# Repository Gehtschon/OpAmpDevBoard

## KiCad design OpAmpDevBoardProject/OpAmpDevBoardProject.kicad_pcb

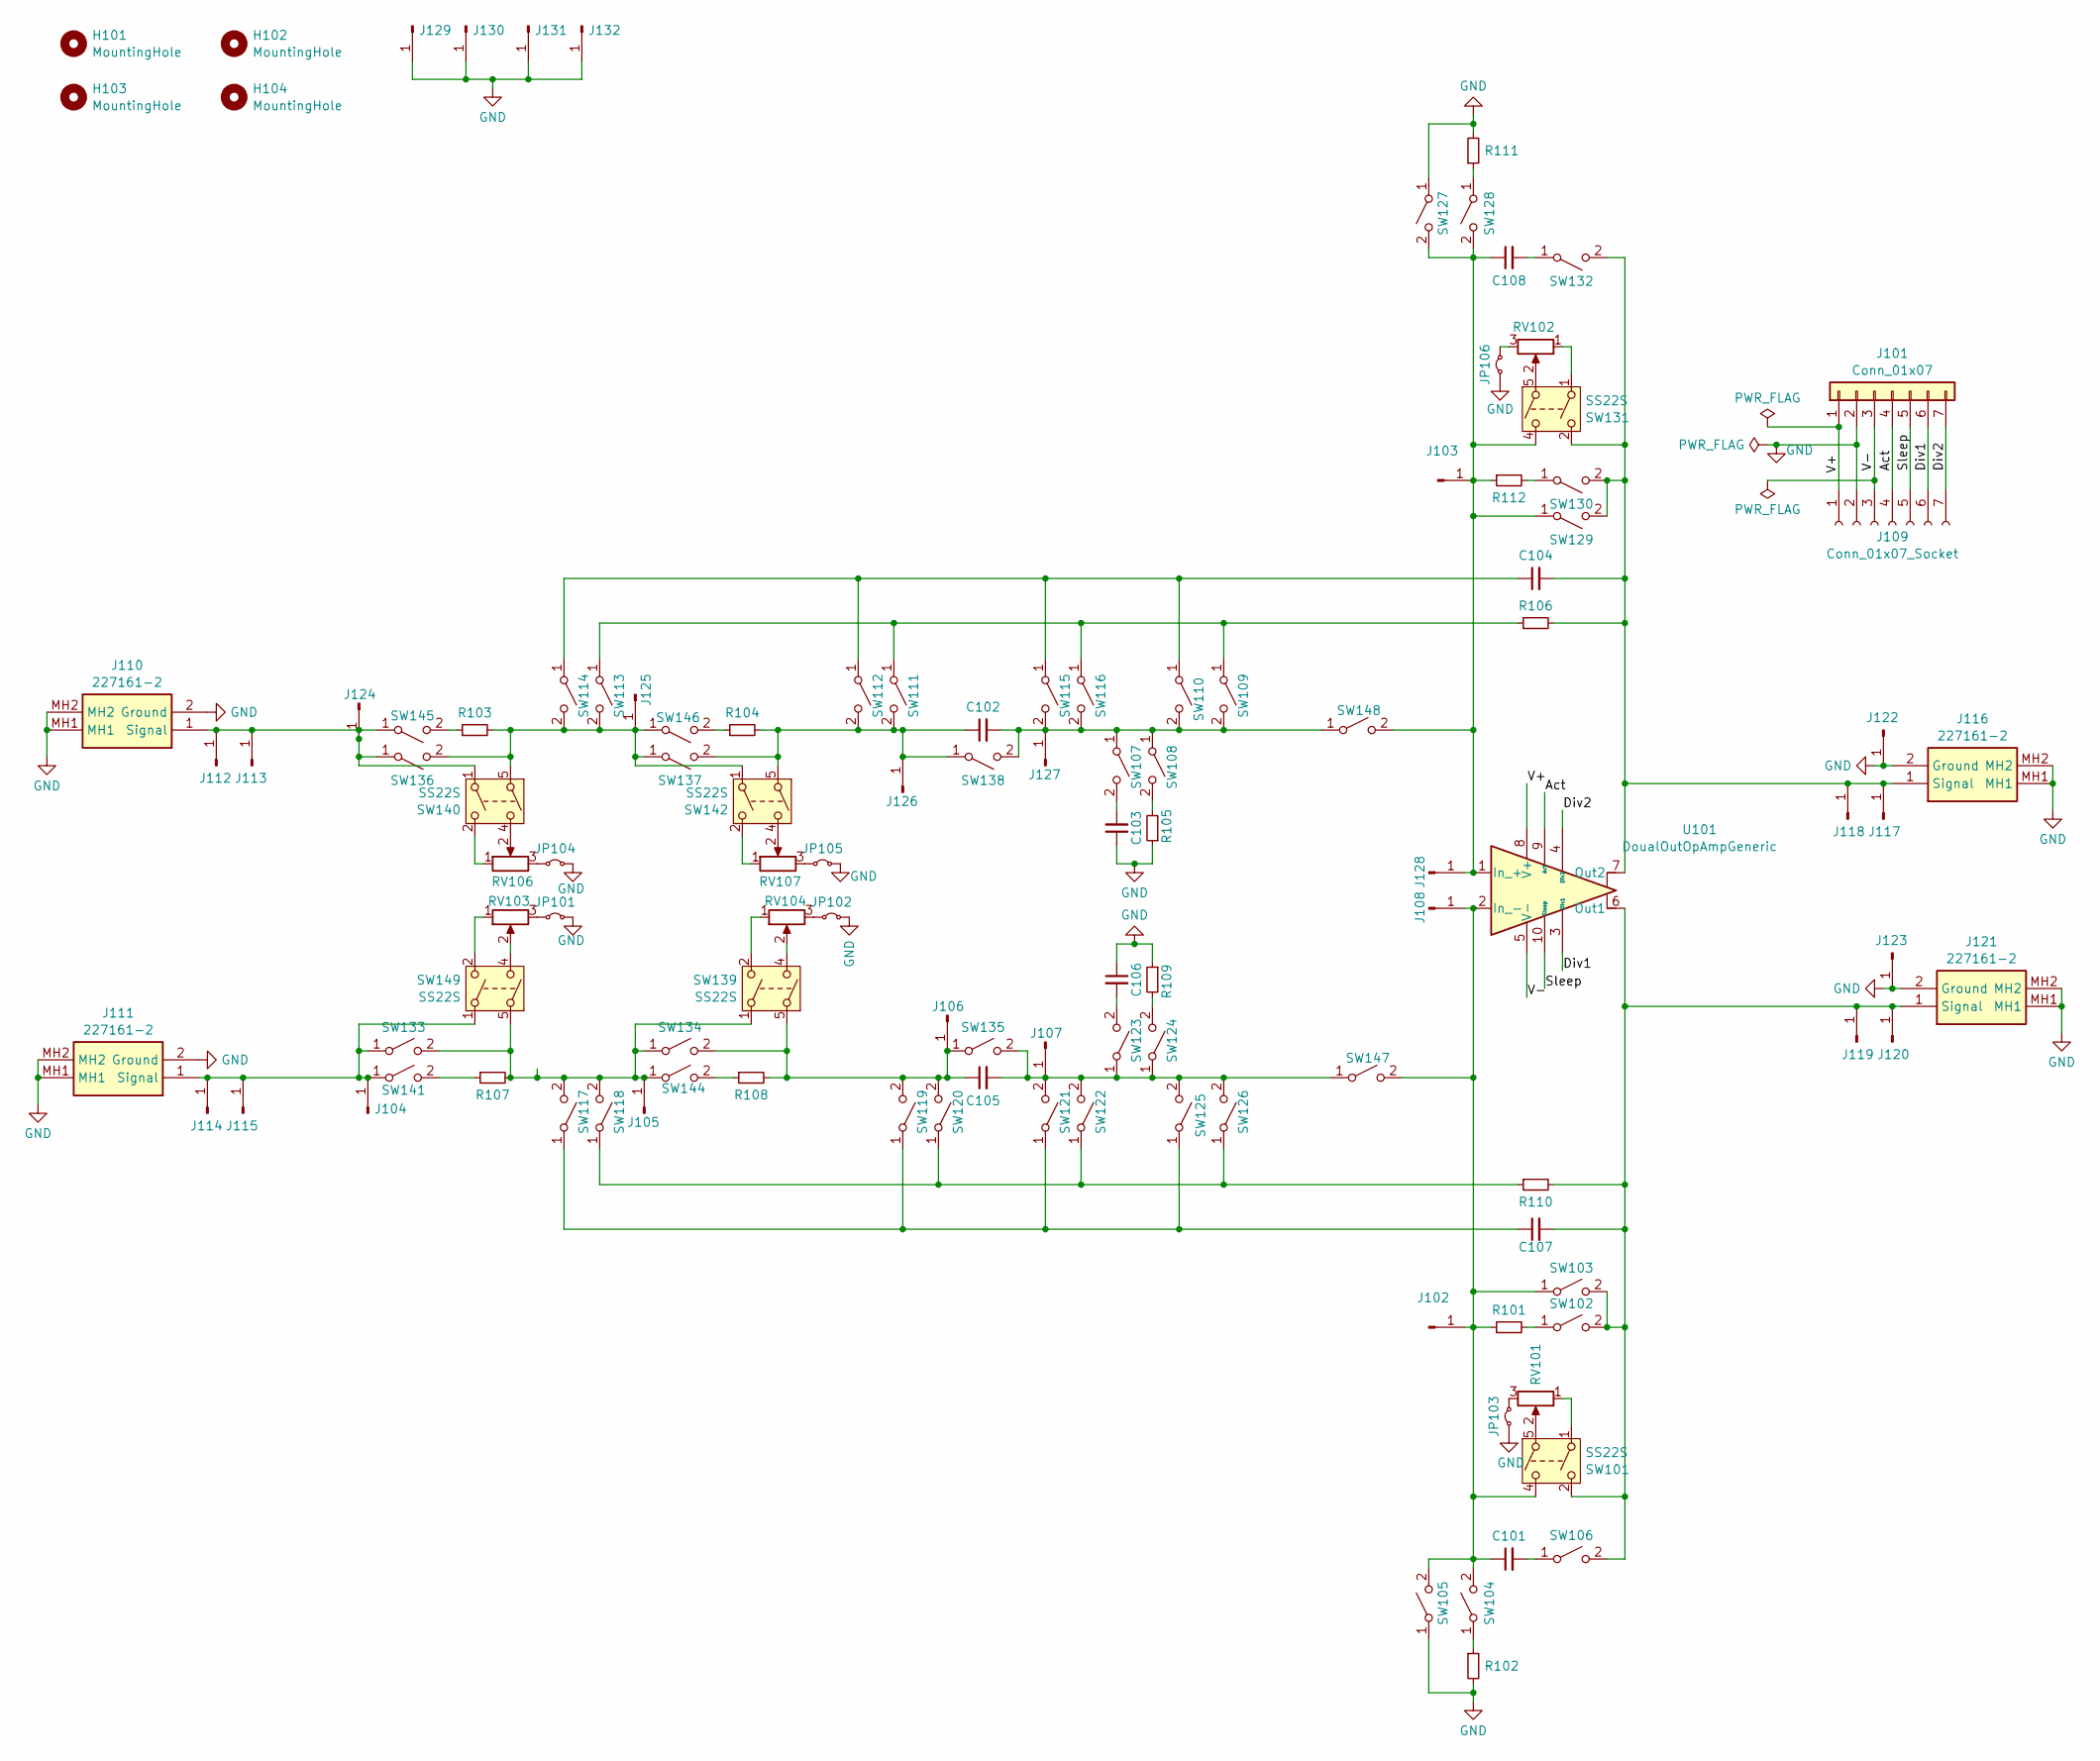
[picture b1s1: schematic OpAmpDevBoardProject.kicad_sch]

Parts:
C101, C102, C103, C104, C105, C106, C107, C108: C_Small; C_0805_2012Metric_Pad1.18x1.45mm_HandSolder
H101, H102, H103, H104: MountingHole; Spacer
J101: Conn_01x07; PinSocket_1x07_P2.54mm_Vertical
J102, J103, J104, J105, J106, J107, J108, J112, J113, J114, J115, J117, J118, J119, J120, J122, J123, J124, J125, J126, J127, J128, J129, J130, J131, J132: Conn_01x01_Pin; PinHeader_1x01_P2.54mm_Vertical
J109: Conn_01x07_Socket; PinHeader_1x07_P2.54mm_Vertical
J110, J111, J116, J121: 227161-2; 2271612; Mouser Part Number 571-2271612
JP101, JP102, JP103, JP104, JP105, JP106: Jumper_2_Small_Bridged; PinHeader_1x02_P2.54mm_Vertical
R101, R102, R103, R104, R105, R106, R107, R108, R109, R110, R111, R112: R_Small; R_0805_2012Metric_Pad1.20x1.40mm_HandSolder
RV101, RV102, RV103, RV104, RV106, RV107: R_Potentiometer; PTV09A-1_Vertical
SW101, SW131, SW139, SW140, SW142, SW149: SS22S; SS22SDP2
SW102, SW103, SW104, SW105, SW106, SW107, SW108, SW109, SW110, SW111, SW112, SW113, SW114, SW115, SW116, SW117, SW118, SW119, SW120, SW121, SW122, SW123, SW124, SW125, SW126, SW127, SW128, SW129, SW130, SW132, SW133, SW134, SW135, SW136, SW137, SW138, SW141, SW144, SW145, SW146, SW147, SW148: SW_SPST; SS12SDP2
U101: DoualOutOpAmpGeneric; OpAmpBoardConnector

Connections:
/Act: J101.4, J109.4, U101.9 (Act)
/Div1: J101.6, J109.6, U101.3 (Div1)
/Div2: J101.7, J109.7, U101.4 (Div2)
/Sleep: J101.5, J109.5, U101.10 (Sleep)
/V+: J101.1, J109.1, U101.8 (V+)
/V-: J101.3, J109.3, U101.5 (V-)
GND: C103.1, C106.1, J101.2, J109.2, J110.2 (Ground), J110.MH1, J110.MH2, J111.2 (Ground), J111.MH1, J111.MH2, J116.2 (Ground), J116.MH1, J116.MH2, J121.2 (Ground), J121.MH1, J121.MH2, J122.1, J123.1, J129.1, J130.1, J131.1, J132.1, JP101.2 (B), JP102.2 (B), JP103.1 (A), JP104.2 (B), JP105.2 (B), JP106.1 (A), R102.2, R105.1, R109.1, R111.2, SW105.1 (A), SW127.1 (A)
unnamed: C101.1, J102.1, J108.1, R101.1, SW101.4, SW103.1 (A), SW104.2 (B), SW105.2 (B), SW147.2 (B), U101.2 (In_-)
unnamed: C108.1, J103.1, J128.1, R112.1, SW127.2 (B), SW128.2 (B), SW129.1 (A), SW131.4, SW148.2 (B), U101.1 (In_+)
unnamed: J104.1, J111.1 (Signal), J114.1, J115.1, SW133.1 (A), SW141.1 (A), SW149.1
unnamed: J105.1, R107.2, SW117.2 (B), SW118.2 (B), SW133.2 (B), SW134.1 (A), SW139.1, SW144.1 (A), SW149.5
unnamed: C105.1, J106.1, R108.2, SW119.2 (B), SW120.2 (B), SW134.2 (B), SW135.1 (A), SW139.5
unnamed: C105.2, J107.1, SW121.2 (B), SW122.2 (B), SW123.1 (A), SW124.1 (A), SW125.2 (B), SW126.2 (B), SW135.2 (B), SW147.1 (A)
unnamed: J110.1 (Signal), J112.1, J113.1, J124.1, SW136.1 (A), SW140.1, SW145.1 (A)
unnamed: C104.2, J116.1 (Signal), J117.1, J118.1, R106.2, SW129.2 (B), SW130.2 (B), SW131.2, SW132.2 (B), U101.7 (Out2)
unnamed: C107.2, J119.1, J120.1, J121.1 (Signal), R110.2, SW101.2, SW102.2 (B), SW103.2 (B), SW106.2 (B), U101.6 (Out1)
unnamed: J125.1, R103.2, SW113.2 (B), SW114.2 (B), SW136.2 (B), SW137.1 (A), SW140.5, SW142.1, SW146.1 (A)
unnamed: C102.1, J126.1, R104.2, SW111.2 (B), SW112.2 (B), SW137.2 (B), SW138.1 (A), SW142.5
unnamed: C102.2, J127.1, SW107.1 (A), SW108.1 (A), SW109.2 (B), SW110.2 (B), SW115.2 (B), SW116.2 (B), SW138.2 (B), SW148.1 (A)
unnamed: JP101.1 (A), RV103.3
unnamed: JP102.1 (A), RV104.3
unnamed: JP103.2 (B), RV101.3
unnamed: JP104.1 (A), RV106.3
unnamed: JP105.1 (A), RV107.3
unnamed: JP106.2 (B), RV102.3
unnamed: RV101.1, SW101.1
unnamed: RV101.2, SW101.5
unnamed: RV102.1, SW131.1
unnamed: RV102.2, SW131.5
unnamed: RV103.1, SW149.2
unnamed: RV103.2, SW149.4
unnamed: RV104.1, SW139.2
unnamed: RV104.2, SW139.4
unnamed: RV106.1, SW140.2
unnamed: RV106.2, SW140.4
unnamed: RV107.1, SW142.2
unnamed: RV107.2, SW142.4
unnamed: R101.2, SW102.1 (A)
unnamed: R102.1, SW104.1 (A)
unnamed: C101.2, SW106.1 (A)
unnamed: C103.2, SW107.2 (B)
unnamed: R105.2, SW108.2 (B)
unnamed: R106.1, SW109.1 (A), SW111.1 (A), SW113.1 (A), SW116.1 (A)
unnamed: C104.1, SW110.1 (A), SW112.1 (A), SW114.1 (A), SW115.1 (A)
unnamed: C107.1, SW117.1 (A), SW119.1 (A), SW121.1 (A), SW125.1 (A)
unnamed: R110.1, SW118.1 (A), SW120.1 (A), SW122.1 (A), SW126.1 (A)
unnamed: C106.2, SW123.2 (B)
unnamed: R109.2, SW124.2 (B)
unnamed: R111.1, SW128.1 (A)
unnamed: R112.2, SW130.1 (A)
unnamed: C108.2, SW132.1 (A)
unnamed: R107.1, SW141.2 (B)
unnamed: R108.1, SW144.2 (B)
unnamed: R103.1, SW145.2 (B)
unnamed: R104.1, SW146.2 (B)

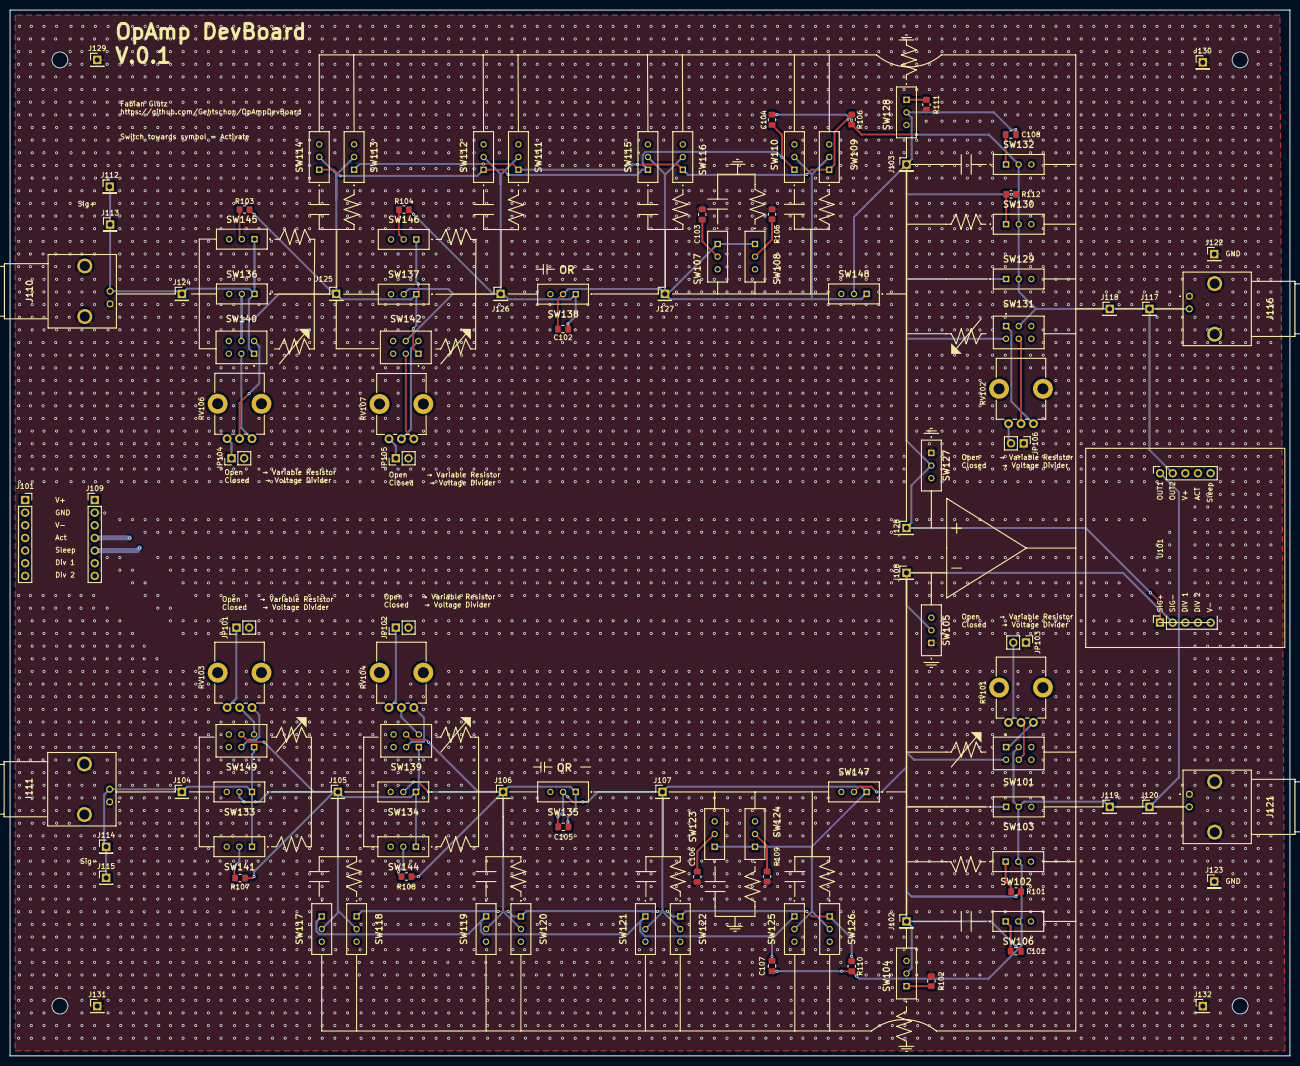
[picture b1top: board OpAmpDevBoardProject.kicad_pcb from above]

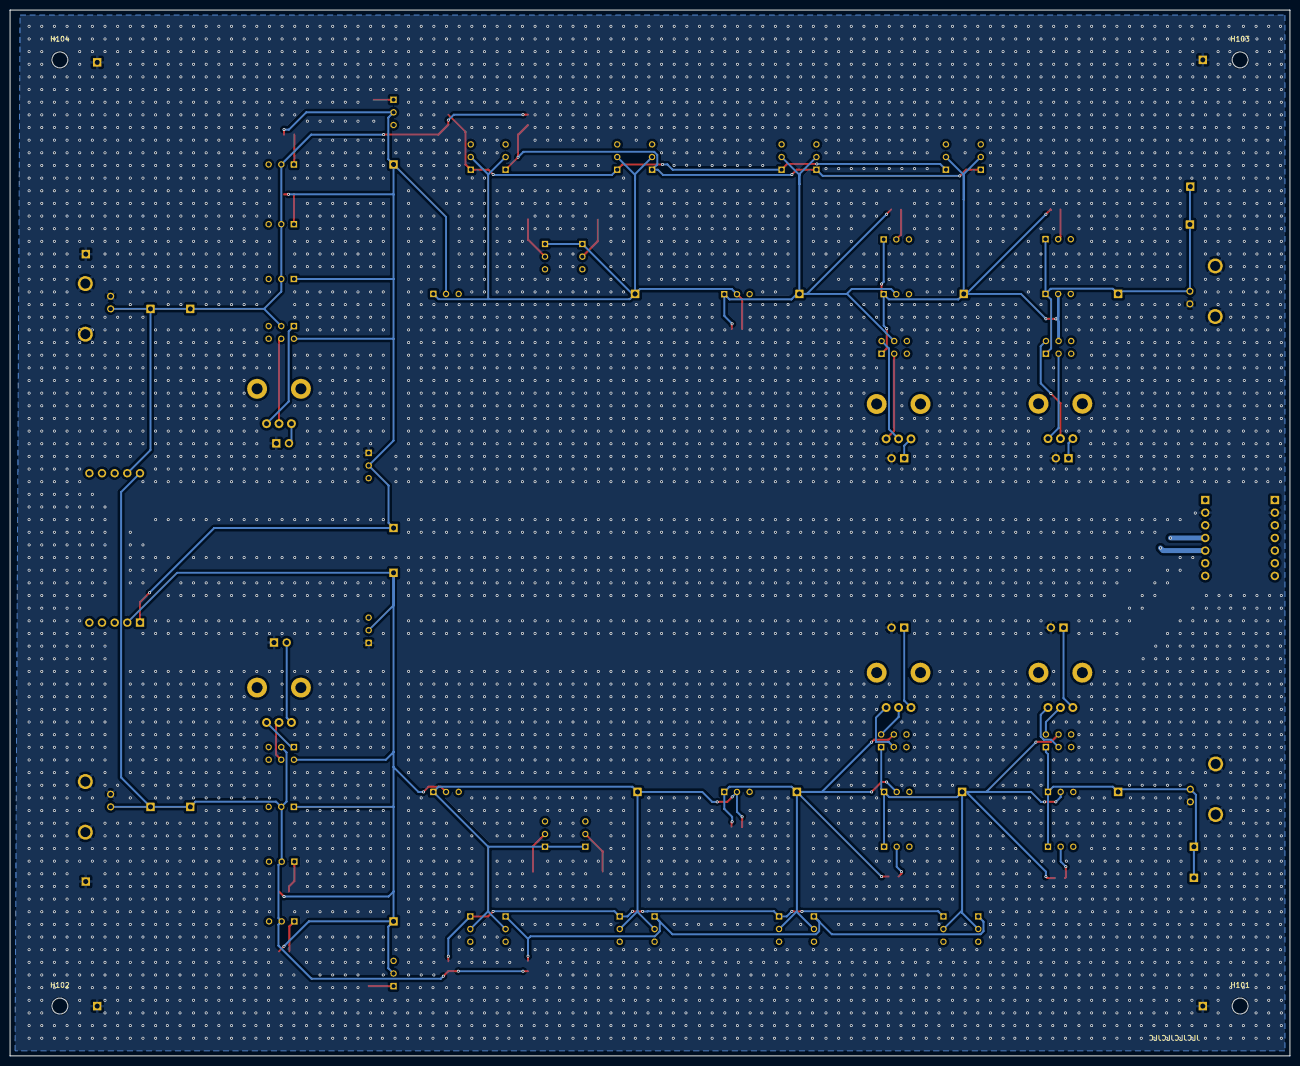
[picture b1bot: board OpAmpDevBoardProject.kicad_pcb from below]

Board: 4 copper layers, 257.0 x 210.0 mm, 117 parts (4 on the bottom side), 55 nets.

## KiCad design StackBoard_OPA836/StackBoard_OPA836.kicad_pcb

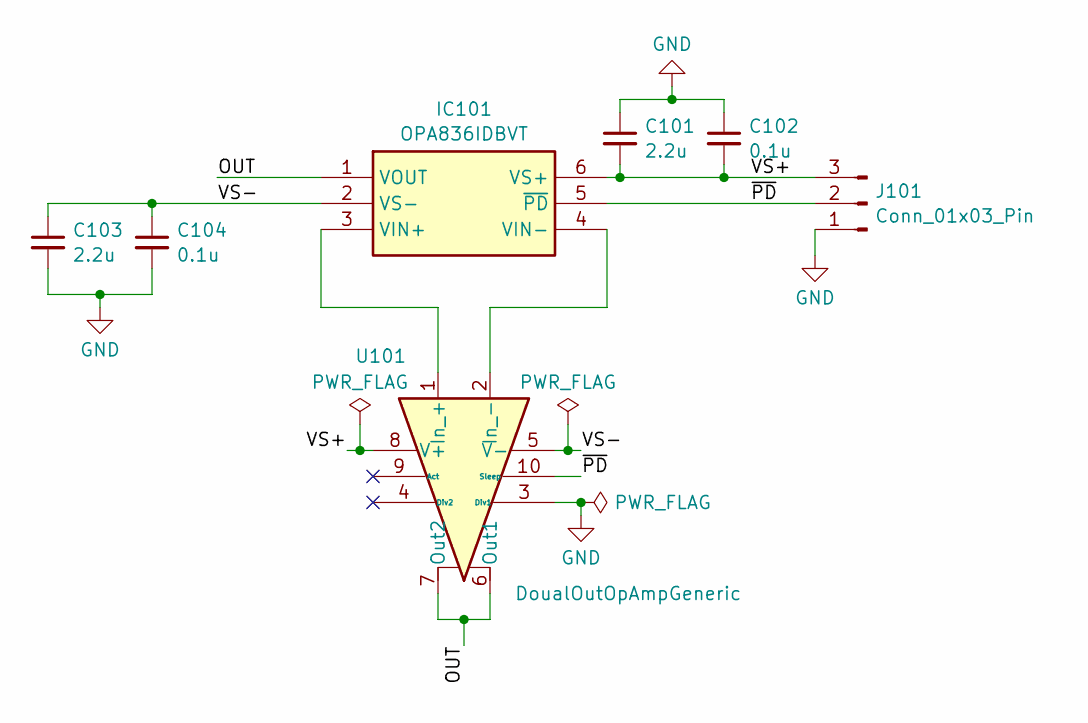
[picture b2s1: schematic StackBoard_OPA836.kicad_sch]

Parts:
C101, C103: 2.2u; C_0805_2012Metric_Pad1.18x1.45mm_HandSolder
C102, C104: 0.1u; C_0805_2012Metric_Pad1.18x1.45mm_HandSolder
IC101: OPA836IDBVT; SOT95P280X145-6N; Mouser Part Number 595-OPA836IDBVT
J101: Conn_01x03_Pin; PinHeader_1x03_P2.54mm_Vertical
U101: DoualOutOpAmpGeneric; OpAmpBoardConnector

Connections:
/OUT: IC101.1 (VOUT), U101.6 (Out1), U101.7 (Out2)
/VS+: C101.2, C102.2, IC101.6 (VS+), J101.3, U101.8 (V+)
/VS-: C103.1, C104.1, IC101.2 (VS-), U101.5 (V-)
/~PD: IC101.5 (~PD), J101.2, U101.10 (Sleep)
GND: C101.1, C102.1, C103.2, C104.2, J101.1, U101.3 (Div1)
unnamed: IC101.3 (VIN+), U101.1 (In_+)
unnamed: IC101.4 (VIN-), U101.2 (In_-)

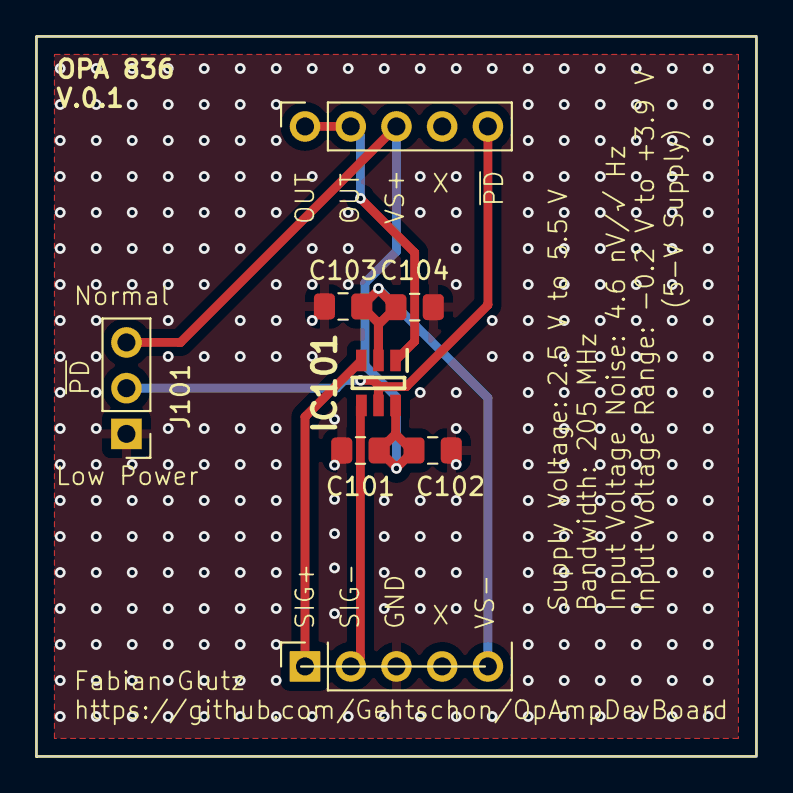
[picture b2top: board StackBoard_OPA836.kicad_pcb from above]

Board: 2 copper layers, 40.0 x 40.0 mm, 7 parts (0 on the bottom side), 7 nets.

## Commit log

2025-08-04 Added license
2025-08-04 opampdesign done
2025-08-07 finished botzh sides
2025-08-08 added double switch and started changing schematic
2025-08-11 late night fu me
2025-08-14 added gnd connectors
2025-08-20 stiching finished
2025-08-21 created JLCPCB manufactoring gerber zip folder
2025-08-21 stiching on OPA836 board done
2025-08-21 created OPA836 gerber files for JLCPCB
2025-08-21 changed Boardtilte and greated gerber again on main board
